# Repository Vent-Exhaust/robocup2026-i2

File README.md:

# robocup2026
# Vent Exhaust - RoboCup Singapore Soccer Infrared Junior 

<!--  -->

*Repository for the official electronic, mechanical, and software files of Vent Exhaust (VE) 1, formerly known as 2 Chairs.*

<p align="center">
  
</p>

## About

This repository is for **Vent Exhaust**, a Singapore RoboCup Infrared Soccer Junior team, and includes relevant design files and resources.

## Repository Structure

- **elec/** - PCB designs, schematics, and component footprints.
- **mech/** - 3D-printable files in **.3MF** and **.STL** formats; includes rendered images of the robot and its mirrored counterpart for reference and other files related to mechanical design.
- **code/** - PlatformIO firmware for the 3-layer robot architecture (Layer 1-3 Teensies / ESP32).
- **cam/** - MicroPython camera firmware (`cam.py`) running on an OpenMV H7 Plus, detecting goals and ball over serial.
- **branding/** - Official team branding and design assets.
- **media/** - Robot photos, gallery thumbnails, screenshots, and reference images used by the README and project documentation.

## Mechanical CAD

- [View the Fusion 360 model](https://a360.co/4tRNy74)

## Robot Gallery

<p align="center">

  <br>

</p>

## Robot Architecture

Three processors communicate over UART using a custom SerialComm packet protocol:

| Layer | Hardware | Role |
|-------|----------|------|
| Layer 1 | Teensy 4.0 | 32-LDR light ring - white line detection |
| Layer 2 | Teensy 4.0 | Main brain - strategy, X-drive motors, IMU heading hold, localisation, scoring |
| Layer 3 | Seeed XIAO ESP32-C3 | 28-IR sensor ring - ball detection + 4 DIP switches |
| Camera | OpenMV H7 Plus (MicroPython) | Dual-goal + ball vision -> serial CSV to Layer 2 |

## Branch Archive

`main` is the active branch. Previous development branches are preserved as
Git tags under `archive/`, such as `archive/i4-v3` and `archive/striker`.

## License & Copyright

Copyright 2026 Vent Exhaust. All rights reserved, except where otherwise stated.

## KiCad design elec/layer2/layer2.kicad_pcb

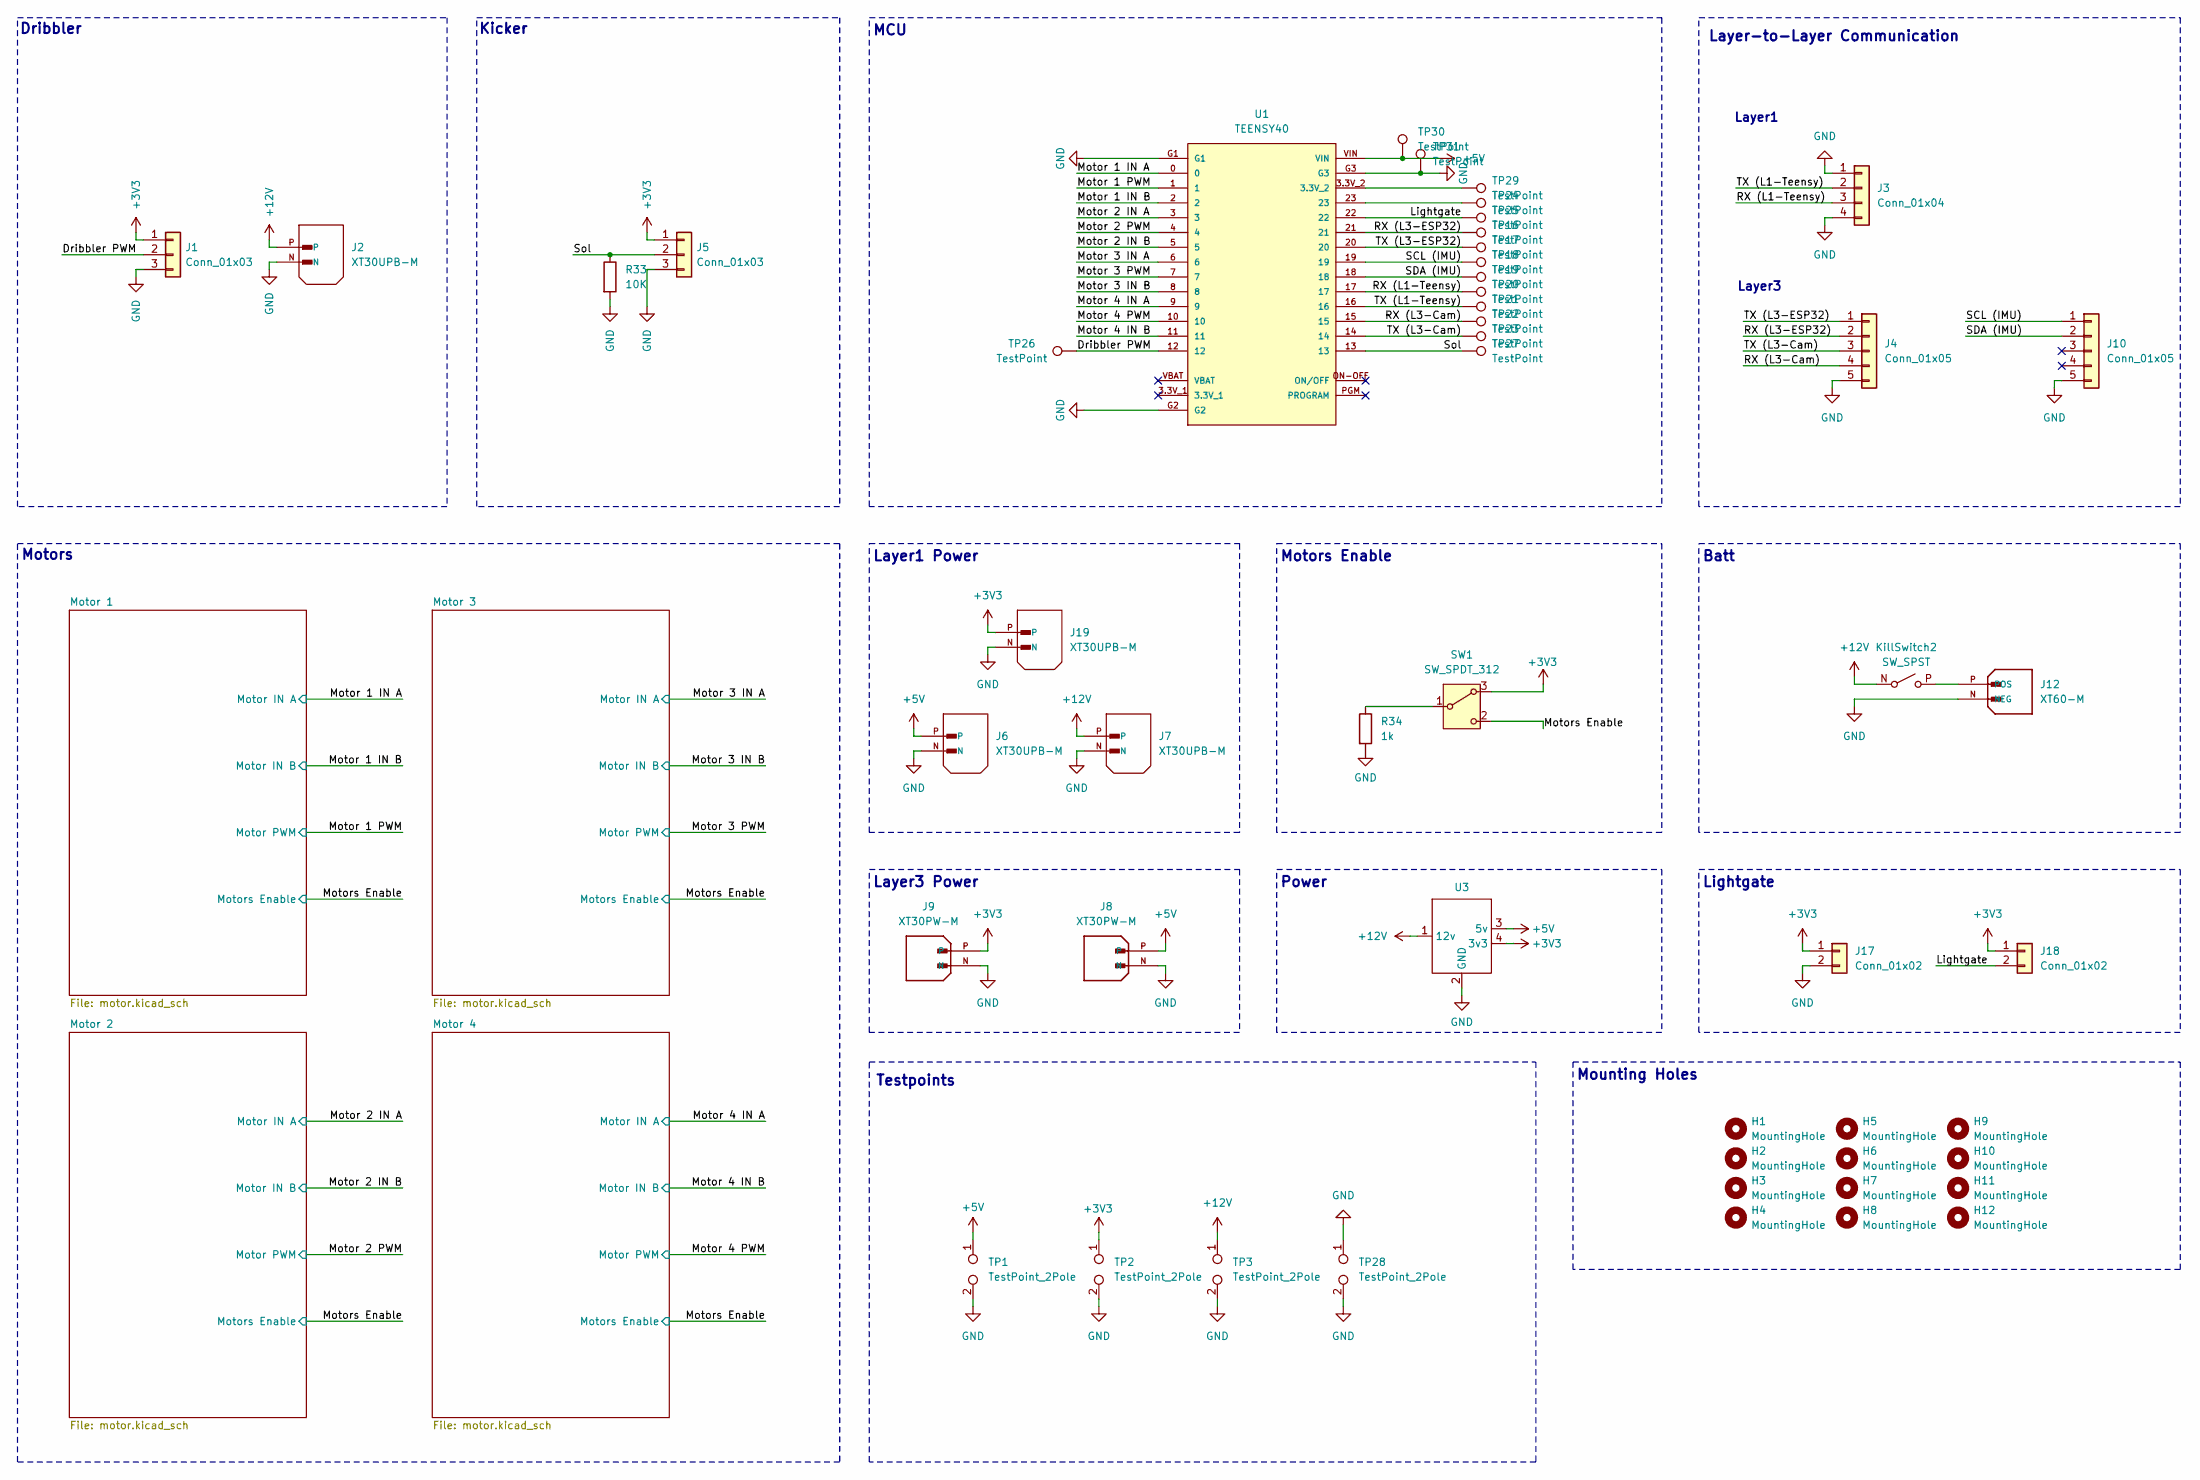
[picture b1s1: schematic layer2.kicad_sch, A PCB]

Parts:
H1, H2, H3, H4, H5, H6, H7, H8, H9, H10, H11, H12: MountingHole; MountingHole_3.2mm_M3_DIN965_Pad
J1, J5: Conn_01x03; JST_XH_B3B-XH-A_1x03_P2.50mm_Vertical
J2, J6, J7, J19: XT30UPB-M; AMASS_XT30UPB-M
J3: Conn_01x04; JST_XH_B4B-XH-A_1x04_P2.50mm_Vertical
J4, J10: Conn_01x05; JST_XH_B5B-XH-A_1x05_P2.50mm_Vertical
J8, J9: XT30PW-M; AMASS_XT30PW-M; PARTREV 1.2
J12: XT60-M; AMASS_XT60-M; PARTREV V1.2
J17, J18: Conn_01x02; JST_XH_B2B-XH-A_1x02_P2.50mm_Vertical
KillSwitch2: SW_SPST; AMASS_XT30UPB-M
R33: 10K; R_0603_1608Metric
R34: 1k; R_0603_1608Metric
SW1: SW_SPDT_312; SS12D00G3
TP1, TP2, TP3, TP28: TestPoint_2Pole; TestPoint_2Pads_Pitch2.54mm_Drill0.8mm
TP16, TP17, TP18, TP19, TP20, TP21, TP22, TP23, TP24, TP25, TP26, TP27, TP29, TP30, TP31: TestPoint; TestPoint_THTPad_D1.5mm_Drill0.7mm
U1: TEENSY40
U3: buck-module

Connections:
+3V3: J1.1, J5.1, J9.P, J17.1, J18.1, J19.P, SW1.3 (A), TP2.1, U3.4 (3v3); also elsewhere on the board
+5V: J6.P, J8.P, TP1.1, TP30.1, U1.VIN, U3.3 (5v)
+12V: J2.P, J7.P, KillSwitch2.N (A), TP3.1, U3.1 (12v); also elsewhere on the board
/Dribbler PWM: J1.2, TP26.1, U1.12
/Lightgate: J18.2, TP25.1, U1.22
/Motor 1 IN A: U1.0; also elsewhere on the board
/Motor 1 IN B: U1.2; also elsewhere on the board
/Motor 1 PWM: U1.1; also elsewhere on the board
/Motor 2 IN A: U1.3; also elsewhere on the board
/Motor 2 IN B: U1.5; also elsewhere on the board
/Motor 2 PWM: U1.4; also elsewhere on the board
/Motor 3 IN A: U1.6; also elsewhere on the board
/Motor 3 IN B: U1.8; also elsewhere on the board
/Motor 3 PWM: U1.7; also elsewhere on the board
/Motor 4 IN A: U1.9; also elsewhere on the board
/Motor 4 IN B: U1.11; also elsewhere on the board
/Motor 4 PWM: U1.10; also elsewhere on the board
/Motors Enable: R34.1, SW1.1 (B); also elsewhere on the board
/RX (L3-Cam: J4.3, TP23.1, U1.14
/RX (L3-ESP32): J4.1, TP17.1, U1.20
/SCL (IMU): J10.1, TP18.1, U1.19
/SDA (IMU): J10.2, TP19.1, U1.18
/Sol: J5.2, R33.1, TP27.1, U1.13
/TX (L3-Cam): J4.4, TP22.1, U1.15
/TX (L3-ESP32): J4.2, TP16.1, U1.21
GND: J1.3, J2.N, J3.1, J3.4, J4.5, J5.3, J6.N, J7.N, J8.N, J9.N, J10.5, J12.N (NEG), J17.2, J19.N, R33.2, R34.2, SW1.2 (C), TP1.2, TP2.2, TP3.2, TP28.1, TP28.2, TP31.1, U1.G1, U1.G2, U1.G3, U3.2 (GND); also elsewhere on the board
unnamed: J12.P (POS), KillSwitch2.P (B)
unnamed: TP24.1, U1.23
unnamed: TP29.1, U1.3.3V_2

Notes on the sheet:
Batt
Mounting Holes
Lightgate
Layer1
Power
Kicker
Dribbler
Motors
Testpoints
MCU
Layer3
Layer1 Power
Motors Enable
Layer-to-Layer Communication
Layer3 Power

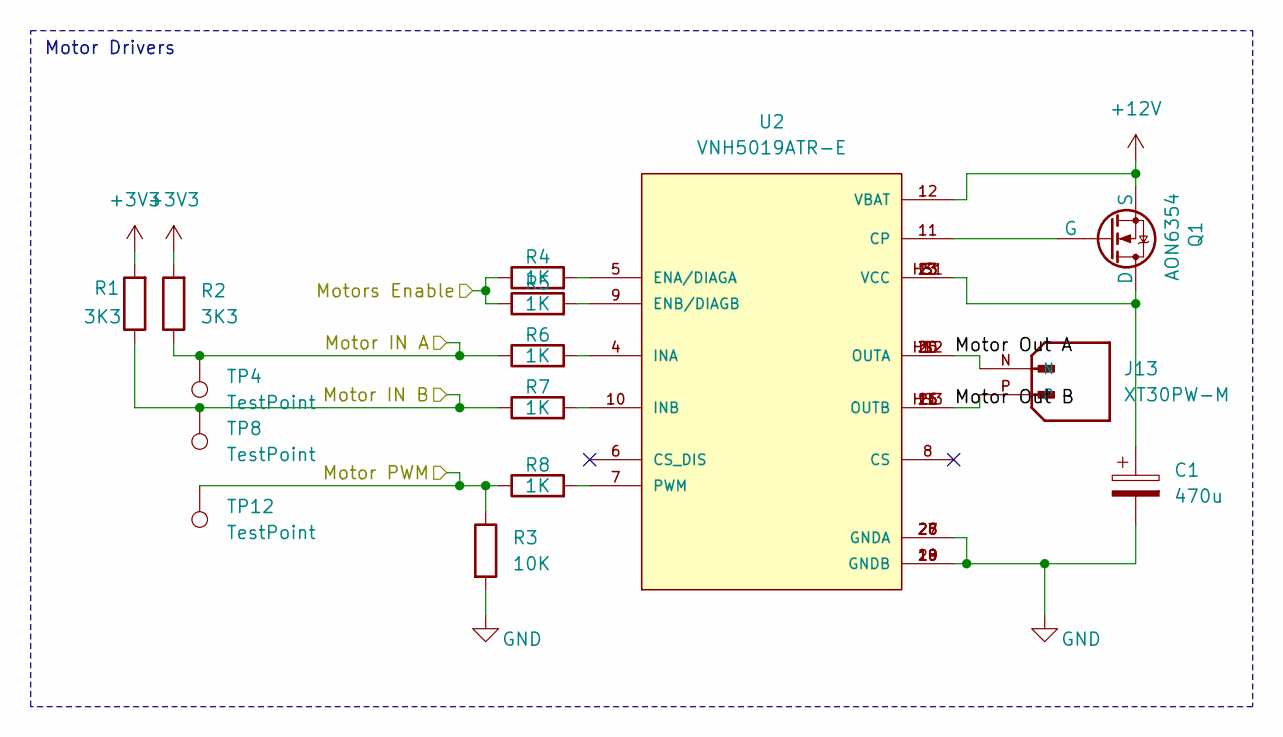
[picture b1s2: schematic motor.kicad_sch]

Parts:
C1: 470u; CP_Radial_D8.0mm_P3.50mm; LCSC C5162352
J13: XT30PW-M; AMASS_XT30PW-M; PARTREV 1.2
Q1: AON6354; 8-DFN (5x6)
R1, R2: 3K3; R_0603_1608Metric
R3: 10K; R_0603_1608Metric
R4, R5, R6, R7, R8: 1K; R_0603_1608Metric
TP4, TP8, TP12: TestPoint
U2: VNH5019ATR-E; PARTREV 11

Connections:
+3V3: R1.2, R2.2; also elsewhere on the board
+12V: Q1.1 (S), Q1.2 (S), Q1.3 (S), U2.12 (VBAT); also elsewhere on the board
/Motor 1 IN A: R2.1, R6.1, TP4.1; also elsewhere on the board
/Motor 1 IN B: R1.1, R7.1, TP8.1; also elsewhere on the board
/Motor 1 PWM: R3.1, R8.1, TP12.1; also elsewhere on the board
/Motor 1/Motor Out A: J13.N, U2.1 (OUTA), U2.25 (OUTA), U2.30 (OUTA), U2.HS2 (OUTA)
/Motor 1/Motor Out B: J13.P, U2.15 (OUTB), U2.16 (OUTB), U2.21 (OUTB), U2.HS3 (OUTB)
/Motors Enable: R4.1, R5.1; also elsewhere on the board
GND: C1.2, R3.2, U2.18 (GNDB), U2.19 (GNDB), U2.20 (GNDB), U2.26 (GNDA), U2.27 (GNDA), U2.28 (GNDA); also elsewhere on the board
unnamed: C1.1, Q1.5 (D), Q1.6 (D), Q1.7 (D), Q1.8 (D), Q1.9 (D), U2.3 (VCC), U2.13 (VCC), U2.23 (VCC), U2.HS1 (VCC)
unnamed: Q1.4 (G), U2.11 (CP)
unnamed: R4.2, U2.5 (ENA/DIAGA)
unnamed: R5.2, U2.9 (ENB/DIAGB)
unnamed: R6.2, U2.4 (INA)
unnamed: R7.2, U2.10 (INB)
unnamed: R8.2, U2.7 (PWM)

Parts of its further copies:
C2, C3, C4: 470u; CP_Radial_D8.0mm_P3.50mm; LCSC C5162352
J14, J15, J16: XT30PW-M; AMASS_XT30PW-M; PARTREV 1.2
Q2, Q3, Q4: AON6354; 8-DFN (5x6)
R9, R10, R17, R18, R25, R26: 3K3; R_0603_1608Metric
R11, R19, R27: 10K; R_0603_1608Metric
R12, R13, R14, R15, R16, R20, R21, R22, R23, R24, R28, R29, R30, R31, R32: 1K; R_0603_1608Metric
TP5, TP6, TP7, TP9, TP10, TP11, TP13, TP14, TP15: TestPoint
U4, U6, U8: VNH5019ATR-E; PARTREV 11

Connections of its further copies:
+3V3: R9.2, R10.2, R17.2, R18.2, R25.2, R26.2; also elsewhere on the board
+12V: Q2.1 (S), Q2.2 (S), Q2.3 (S), Q3.1 (S), Q3.2 (S), Q3.3 (S), Q4.1 (S), Q4.2 (S), Q4.3 (S), U4.12 (VBAT), U6.12 (VBAT), U8.12 (VBAT); also elsewhere on the board
/Motor 2 IN A: R10.1, R14.1, TP5.1; also elsewhere on the board
/Motor 2 IN B: R9.1, R15.1, TP9.1; also elsewhere on the board
/Motor 2 PWM: R11.1, R16.1, TP13.1; also elsewhere on the board
/Motor 2/Motor Out A: J14.N, U4.1 (OUTA), U4.25 (OUTA), U4.30 (OUTA), U4.HS2 (OUTA)
/Motor 2/Motor Out B: J14.P, U4.15 (OUTB), U4.16 (OUTB), U4.21 (OUTB), U4.HS3 (OUTB)
/Motor 3 IN A: R18.1, R22.1, TP6.1; also elsewhere on the board
/Motor 3 IN B: R17.1, R23.1, TP10.1; also elsewhere on the board
/Motor 3 PWM: R19.1, R24.1, TP14.1; also elsewhere on the board
/Motor 3/Motor Out A: J15.N, U6.1 (OUTA), U6.25 (OUTA), U6.30 (OUTA), U6.HS2 (OUTA)
/Motor 3/Motor Out B: J15.P, U6.15 (OUTB), U6.16 (OUTB), U6.21 (OUTB), U6.HS3 (OUTB)
/Motor 4 IN A: R26.1, R30.1, TP7.1; also elsewhere on the board
/Motor 4 IN B: R25.1, R31.1, TP11.1; also elsewhere on the board
/Motor 4 PWM: R27.1, R32.1, TP15.1; also elsewhere on the board
/Motor 4/Motor Out A: J16.N, U8.1 (OUTA), U8.25 (OUTA), U8.30 (OUTA), U8.HS2 (OUTA)
/Motor 4/Motor Out B: J16.P, U8.15 (OUTB), U8.16 (OUTB), U8.21 (OUTB), U8.HS3 (OUTB)
/Motors Enable: R12.1, R13.1, R20.1, R21.1, R28.1, R29.1; also elsewhere on the board
GND: C2.2, C3.2, C4.2, R11.2, R19.2, R27.2, U4.18 (GNDB), U4.19 (GNDB), U4.20 (GNDB), U4.26 (GNDA), U4.27 (GNDA), U4.28 (GNDA), U6.18 (GNDB), U6.19 (GNDB), U6.20 (GNDB), U6.26 (GNDA), U6.27 (GNDA), U6.28 (GNDA), U8.18 (GNDB), U8.19 (GNDB), U8.20 (GNDB), U8.26 (GNDA), U8.27 (GNDA), U8.28 (GNDA); also elsewhere on the board
unnamed: C2.1, Q2.5 (D), Q2.6 (D), Q2.7 (D), Q2.8 (D), Q2.9 (D), U4.3 (VCC), U4.13 (VCC), U4.23 (VCC), U4.HS1 (VCC)
unnamed: C3.1, Q3.5 (D), Q3.6 (D), Q3.7 (D), Q3.8 (D), Q3.9 (D), U6.3 (VCC), U6.13 (VCC), U6.23 (VCC), U6.HS1 (VCC)
unnamed: C4.1, Q4.5 (D), Q4.6 (D), Q4.7 (D), Q4.8 (D), Q4.9 (D), U8.3 (VCC), U8.13 (VCC), U8.23 (VCC), U8.HS1 (VCC)
unnamed: Q2.4 (G), U4.11 (CP)
unnamed: Q3.4 (G), U6.11 (CP)
unnamed: Q4.4 (G), U8.11 (CP)
unnamed: R12.2, U4.5 (ENA/DIAGA)
unnamed: R13.2, U4.9 (ENB/DIAGB)
unnamed: R14.2, U4.4 (INA)
unnamed: R15.2, U4.10 (INB)
unnamed: R16.2, U4.7 (PWM)
unnamed: R20.2, U6.5 (ENA/DIAGA)
unnamed: R21.2, U6.9 (ENB/DIAGB)
unnamed: R22.2, U6.4 (INA)
unnamed: R23.2, U6.10 (INB)
unnamed: R24.2, U6.7 (PWM)
unnamed: R28.2, U8.5 (ENA/DIAGA)
unnamed: R29.2, U8.9 (ENB/DIAGB)
unnamed: R30.2, U8.4 (INA)
unnamed: R31.2, U8.10 (INB)
unnamed: R32.2, U8.7 (PWM)

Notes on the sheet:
Motor Drivers

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
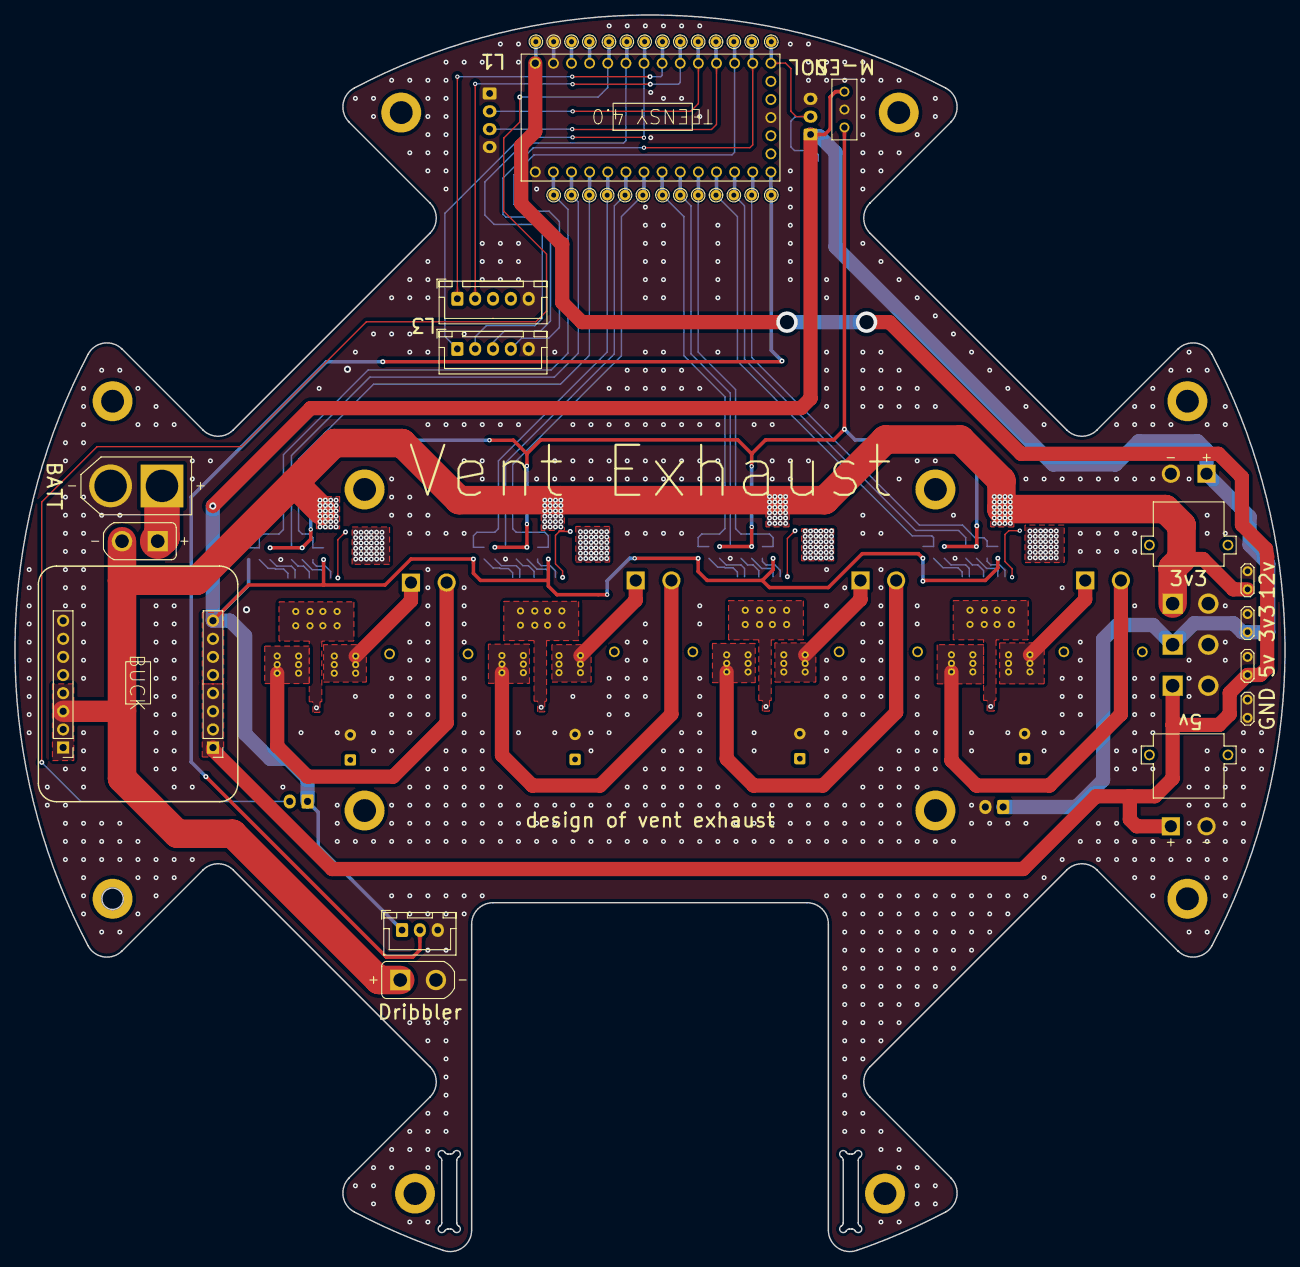
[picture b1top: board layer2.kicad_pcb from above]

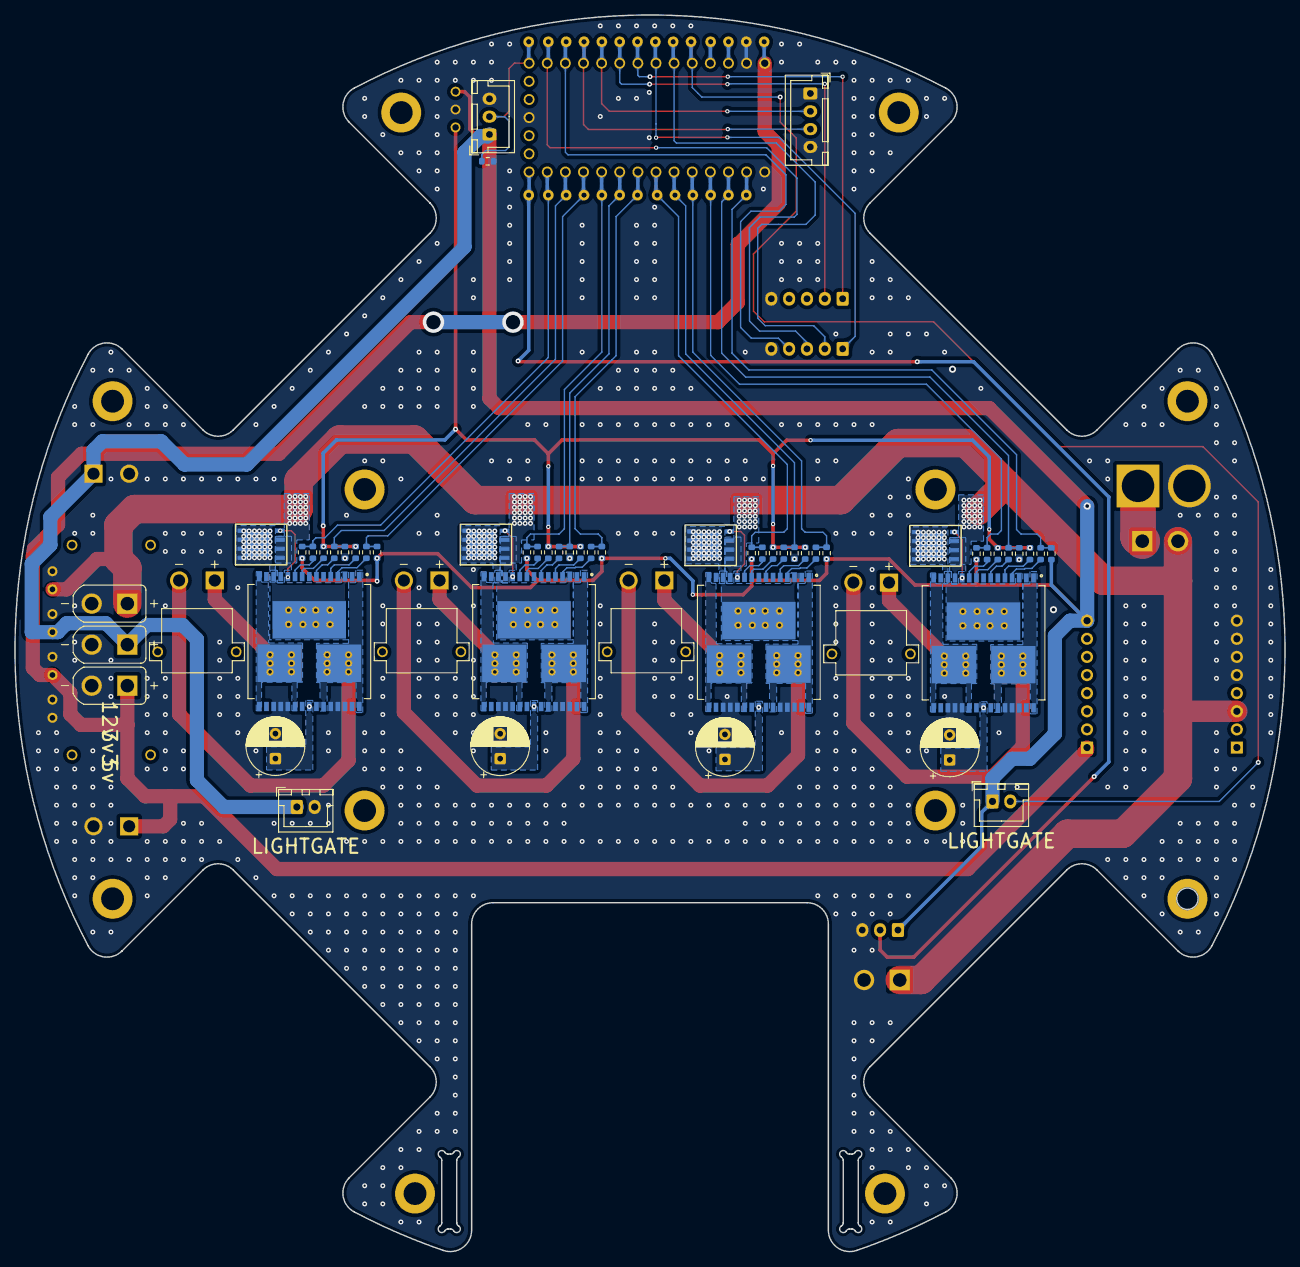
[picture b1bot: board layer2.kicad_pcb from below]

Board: 2 copper layers, 178.0 x 173.3 mm, 110 parts (56 on the bottom side), 67 nets.

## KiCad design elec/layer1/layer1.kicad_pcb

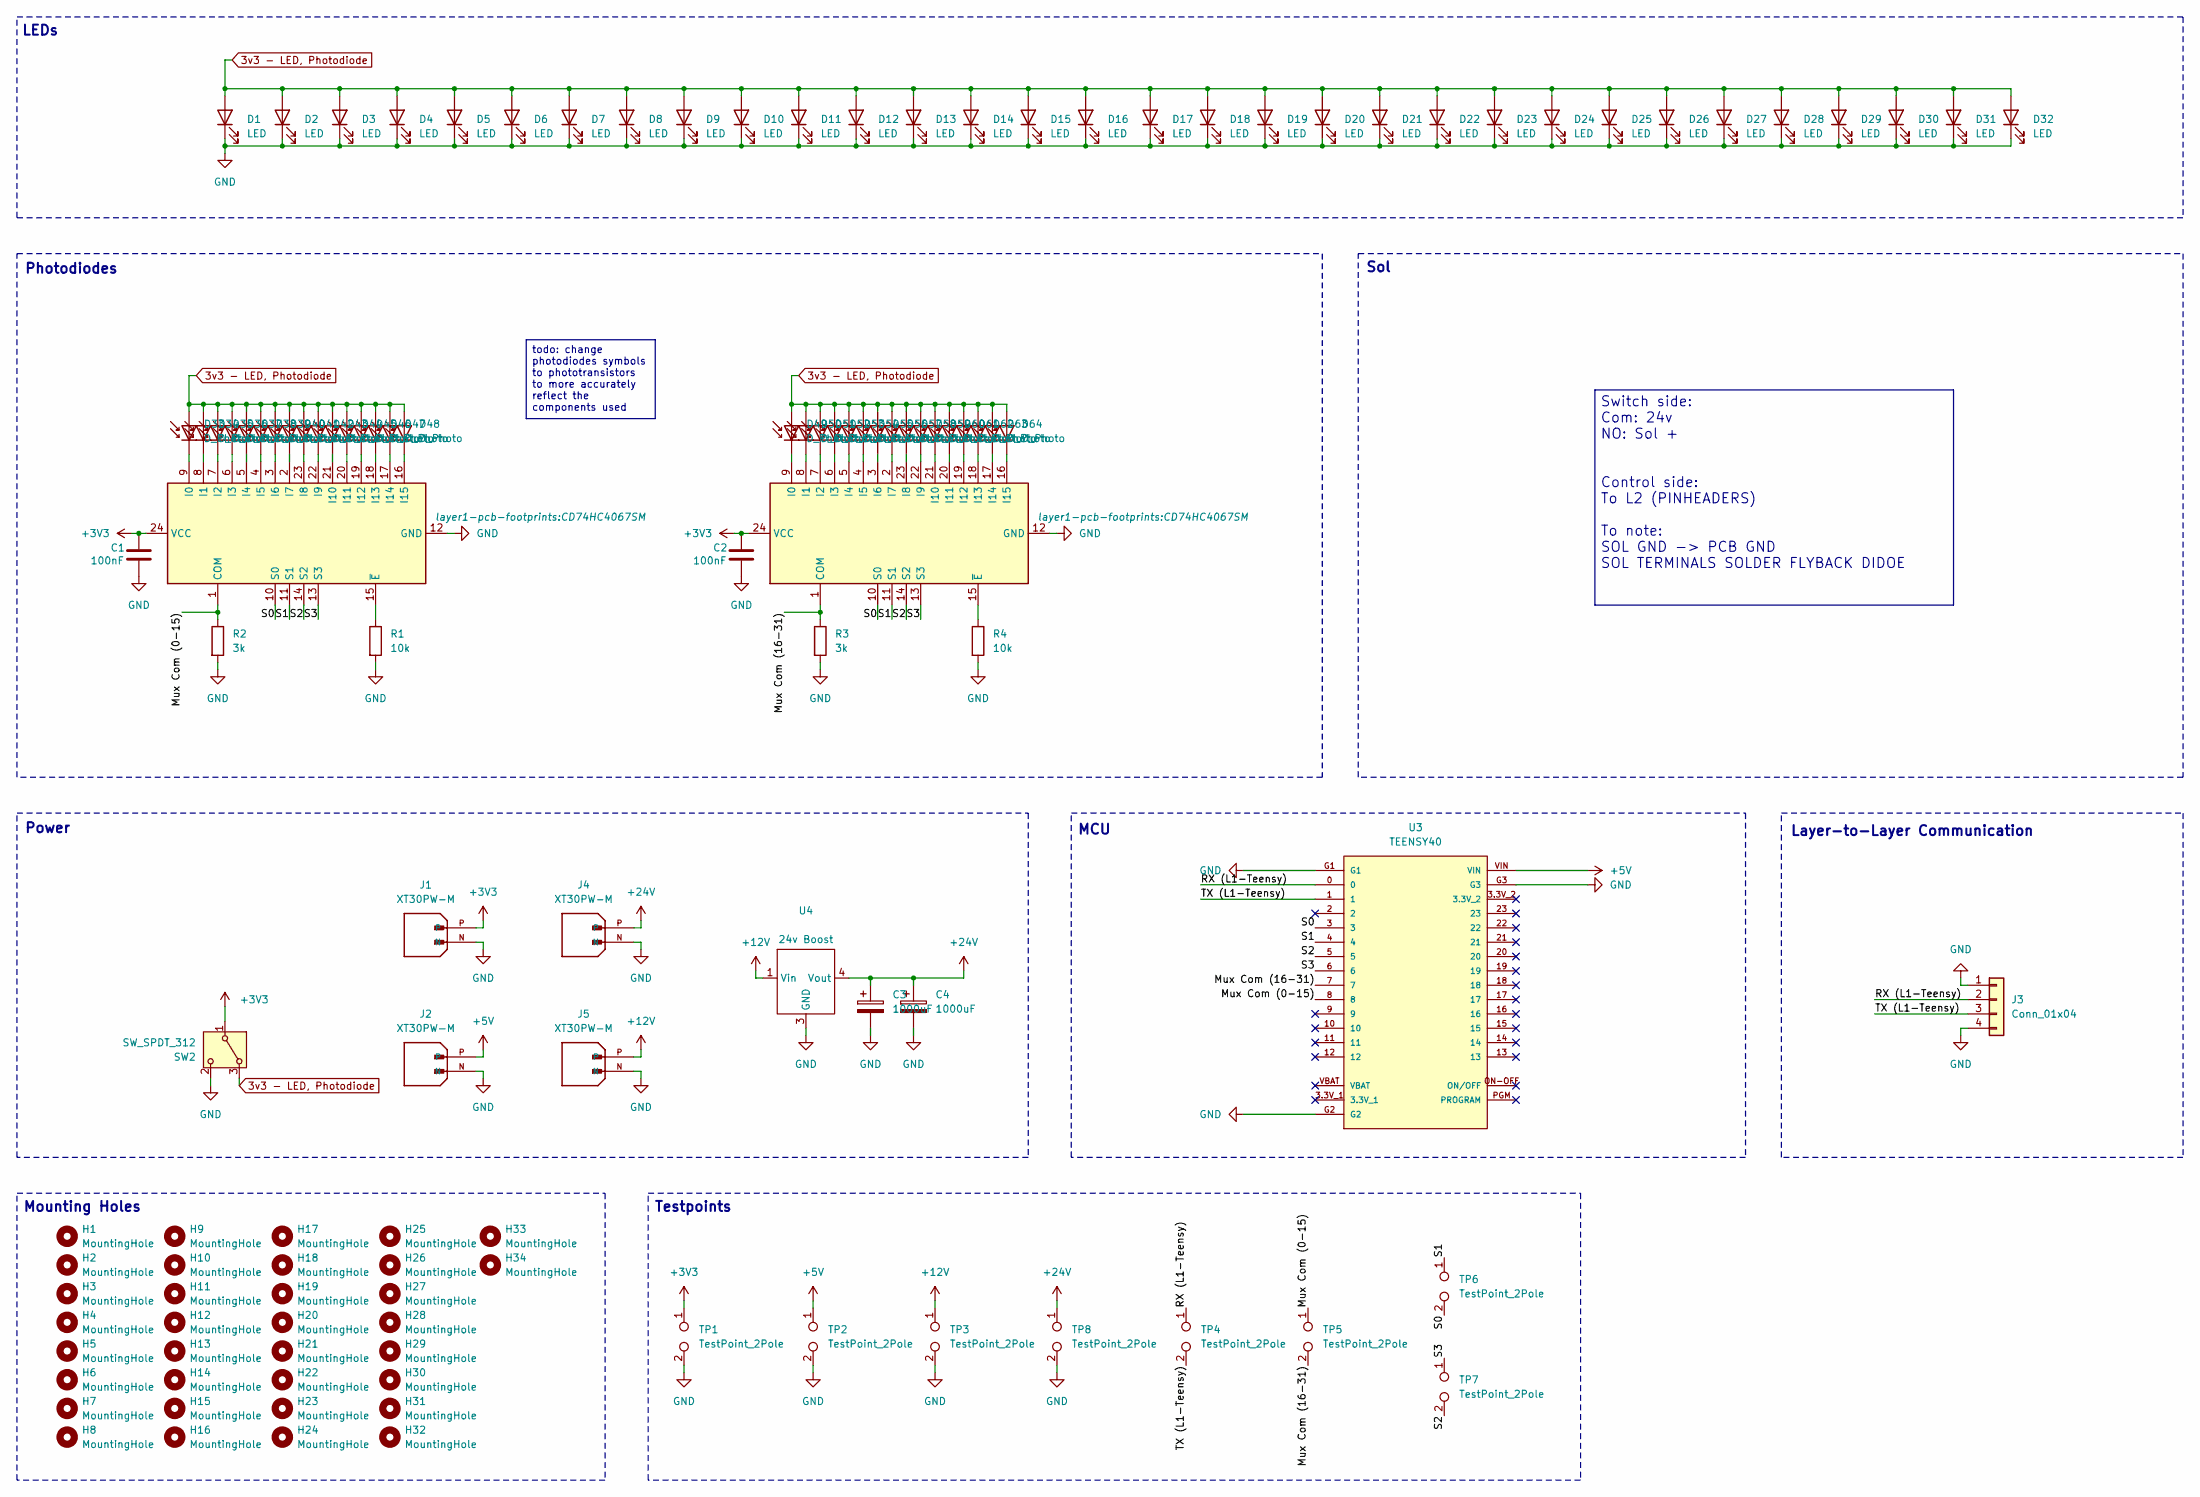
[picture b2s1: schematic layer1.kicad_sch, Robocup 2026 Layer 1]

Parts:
C1, C2: 100nF; C_0603_1608Metric
C3, C4: 1000uF; CP_Radial_D16.0mm_P7.50mm
D1, D2, D3, D4, D5, D6, D7, D8, D9, D10, D11, D12, D13, D14, D15, D16, D17, D18, D19, D20, D21, D22, D23, D24, D25, D26, D27, D28, D29, D30, D31, D32: LED; LED_PLCC_2835
D33, D34, D35, D36, D37, D38, D39, D40, D41, D42, D43, D44, D45, D46, D47, D48, D49, D50, D51, D52, D53, D54, D55, D56, D57, D58, D59, D60, D61, D62, D63, D64: D_Photo; D_0603_1608Metric
H1, H2, H33, H34: MountingHole; MountingHole_2.2mm_M2_DIN965_Pad_TopBottom
H3, H4, H5, H6, H7, H8, H9, H10, H11, H12, H13, H14, H15, H16, H17, H18, H19, H20, H21, H22, H23, H24, H25, H26, H27, H28, H29, H30, H31, H32: MountingHole; MountingHole_3.2mm_M3_DIN965_Pad_TopBottom
J1, J2, J4, J5: XT30PW-M; AMASS_XT30PW-M; PARTREV 1.2
J3: Conn_01x04; JST_XH_B4B-XH-AM_1x04_P2.50mm_Vertical
R1, R4: 10k; C_0603_1608Metric
R2, R3: 3k; C_0603_1608Metric
SW2: SW_SPDT_312; JST_XH_B3B-XH-A_1x03_P2.50mm_Vertical
TP1, TP2, TP3, TP4, TP5, TP6, TP7, TP8: TestPoint_2Pole; TestPoint_2Pads_Pitch2.54mm_Drill0.8mm
U1, U2: CD74HC4067SM
U3: TEENSY40
U4: boost-module

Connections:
3v3 - LED, Photodiode: D1.2 (A), D2.2 (A), D3.2 (A), D4.2 (A), D5.2 (A), D6.2 (A), D7.2 (A), D8.2 (A), D9.2 (A), D10.2 (A), D11.2 (A), D12.2 (A), D13.2 (A), D14.2 (A), D15.2 (A), D16.2 (A), D17.2 (A), D18.2 (A), D19.2 (A), D20.2 (A), D21.2 (A), D22.2 (A), D23.2 (A), D24.2 (A), D25.2 (A), D26.2 (A), D27.2 (A), D28.2 (A), D29.2 (A), D30.2 (A), D31.2 (A), D32.2 (A), D33.2 (A), D34.2 (A), D35.2 (A), D36.2 (A), D37.2 (A), D38.2 (A), D39.2 (A), D40.2 (A), D41.2 (A), D42.2 (A), D43.2 (A), D44.2 (A), D45.2 (A), D46.2 (A), D47.2 (A), D48.2 (A), D49.2 (A), D50.2 (A), D51.2 (A), D52.2 (A), D53.2 (A), D54.2 (A), D55.2 (A), D56.2 (A), D57.2 (A), D58.2 (A), D59.2 (A), D60.2 (A), D61.2 (A), D62.2 (A), D63.2 (A), D64.2 (A), SW2.3 (A)
+3V3: C1.1, C2.1, J1.P, SW2.1 (B), TP1.1, U1.24 (VCC), U2.24 (VCC)
+5V: J2.P, TP2.1, U3.VIN
+12V: J5.P, TP3.1, U4.1 (Vin)
+24V: C3.1, C4.1, J4.P, TP8.1, U4.4 (Vout)
/Mux Com (0-15): R2.1, TP5.1, U1.1 (COM), U3.8
/Mux Com (16-31): R3.1, TP5.2, U2.1 (COM), U3.7
/RX (L1-Teensy): J3.2, TP4.1, U3.0
/S0: TP6.2, U1.10 (S0), U2.10 (S0), U3.3
/S1: TP6.1, U1.11 (S1), U2.11 (S1), U3.4
/S2: TP7.2, U1.14 (S2), U2.14 (S2), U3.5
/S3: TP7.1, U1.13 (S3), U2.13 (S3), U3.6
/TX (L1-Teensy): J3.3, TP4.2, U3.1
GND: C1.2, C2.2, C3.2, C4.2, D1.1 (K), D2.1 (K), D3.1 (K), D4.1 (K), D5.1 (K), D6.1 (K), D7.1 (K), D8.1 (K), D9.1 (K), D10.1 (K), D11.1 (K), D12.1 (K), D13.1 (K), D14.1 (K), D15.1 (K), D16.1 (K), D17.1 (K), D18.1 (K), D19.1 (K), D20.1 (K), D21.1 (K), D22.1 (K), D23.1 (K), D24.1 (K), D25.1 (K), D26.1 (K), D27.1 (K), D28.1 (K), D29.1 (K), D30.1 (K), D31.1 (K), D32.1 (K), J1.N, J2.N, J3.1, J3.4, J4.N, J5.N, R1.2, R2.2, R3.2, R4.2, SW2.2 (C), TP1.2, TP2.2, TP3.2, TP8.2, U1.12 (GND), U2.12 (GND), U3.G1, U3.G2, U3.G3, U4.3 (GND)
unnamed: D33.1 (K), U1.9 (I0)
unnamed: D34.1 (K), U1.8 (I1)
unnamed: D35.1 (K), U1.7 (I2)
unnamed: D36.1 (K), U1.6 (I3)
unnamed: D37.1 (K), U1.5 (I4)
unnamed: D38.1 (K), U1.4 (I5)
unnamed: D39.1 (K), U1.3 (I6)
unnamed: D40.1 (K), U1.2 (I7)
unnamed: D41.1 (K), U1.23 (I8)
unnamed: D42.1 (K), U1.22 (I9)
unnamed: D43.1 (K), U1.21 (I10)
unnamed: D44.1 (K), U1.20 (I11)
unnamed: D45.1 (K), U1.19 (I12)
unnamed: D46.1 (K), U1.18 (I13)
unnamed: D47.1 (K), U1.17 (I14)
unnamed: D48.1 (K), U1.16 (I15)
unnamed: D49.1 (K), U2.9 (I0)
unnamed: D50.1 (K), U2.8 (I1)
unnamed: D51.1 (K), U2.7 (I2)
unnamed: D52.1 (K), U2.6 (I3)
unnamed: D53.1 (K), U2.5 (I4)
unnamed: D54.1 (K), U2.4 (I5)
unnamed: D55.1 (K), U2.3 (I6)
unnamed: D56.1 (K), U2.2 (I7)
unnamed: D57.1 (K), U2.23 (I8)
unnamed: D58.1 (K), U2.22 (I9)
unnamed: D59.1 (K), U2.21 (I10)
unnamed: D60.1 (K), U2.20 (I11)
unnamed: D61.1 (K), U2.19 (I12)
unnamed: D62.1 (K), U2.18 (I13)
unnamed: D63.1 (K), U2.17 (I14)
unnamed: D64.1 (K), U2.16 (I15)
unnamed: R1.1, U1.15 (~E)
unnamed: R4.1, U2.15 (~E)

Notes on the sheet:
Layer-to-Layer Communication
Testpoints
MCU
Power
Mounting Holes
LEDs
Photodiodes
Sol
todo: change photodiodes symbols to phototransistors to more accurately reflect the components used
Switch side: Com: 24v NO: Sol + Control side: To L2 (PINHEADERS) To note: SOL GND -> PCB GND SOL TERMINALS SOLDER FLYBACK DIDOE

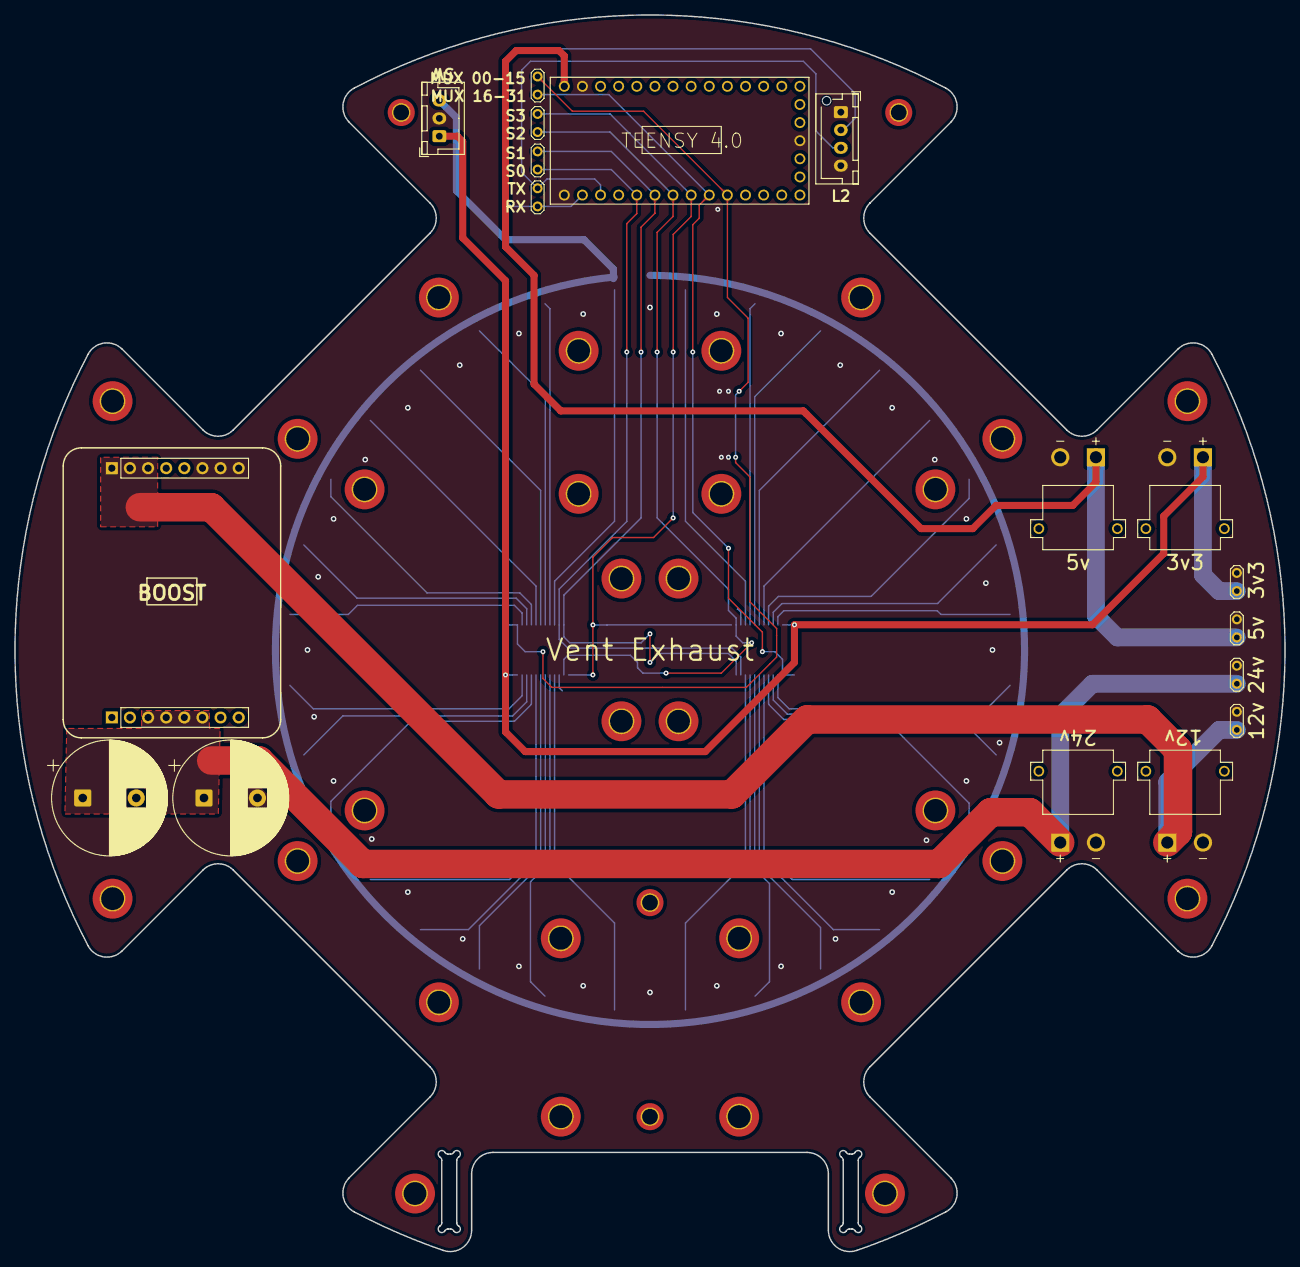
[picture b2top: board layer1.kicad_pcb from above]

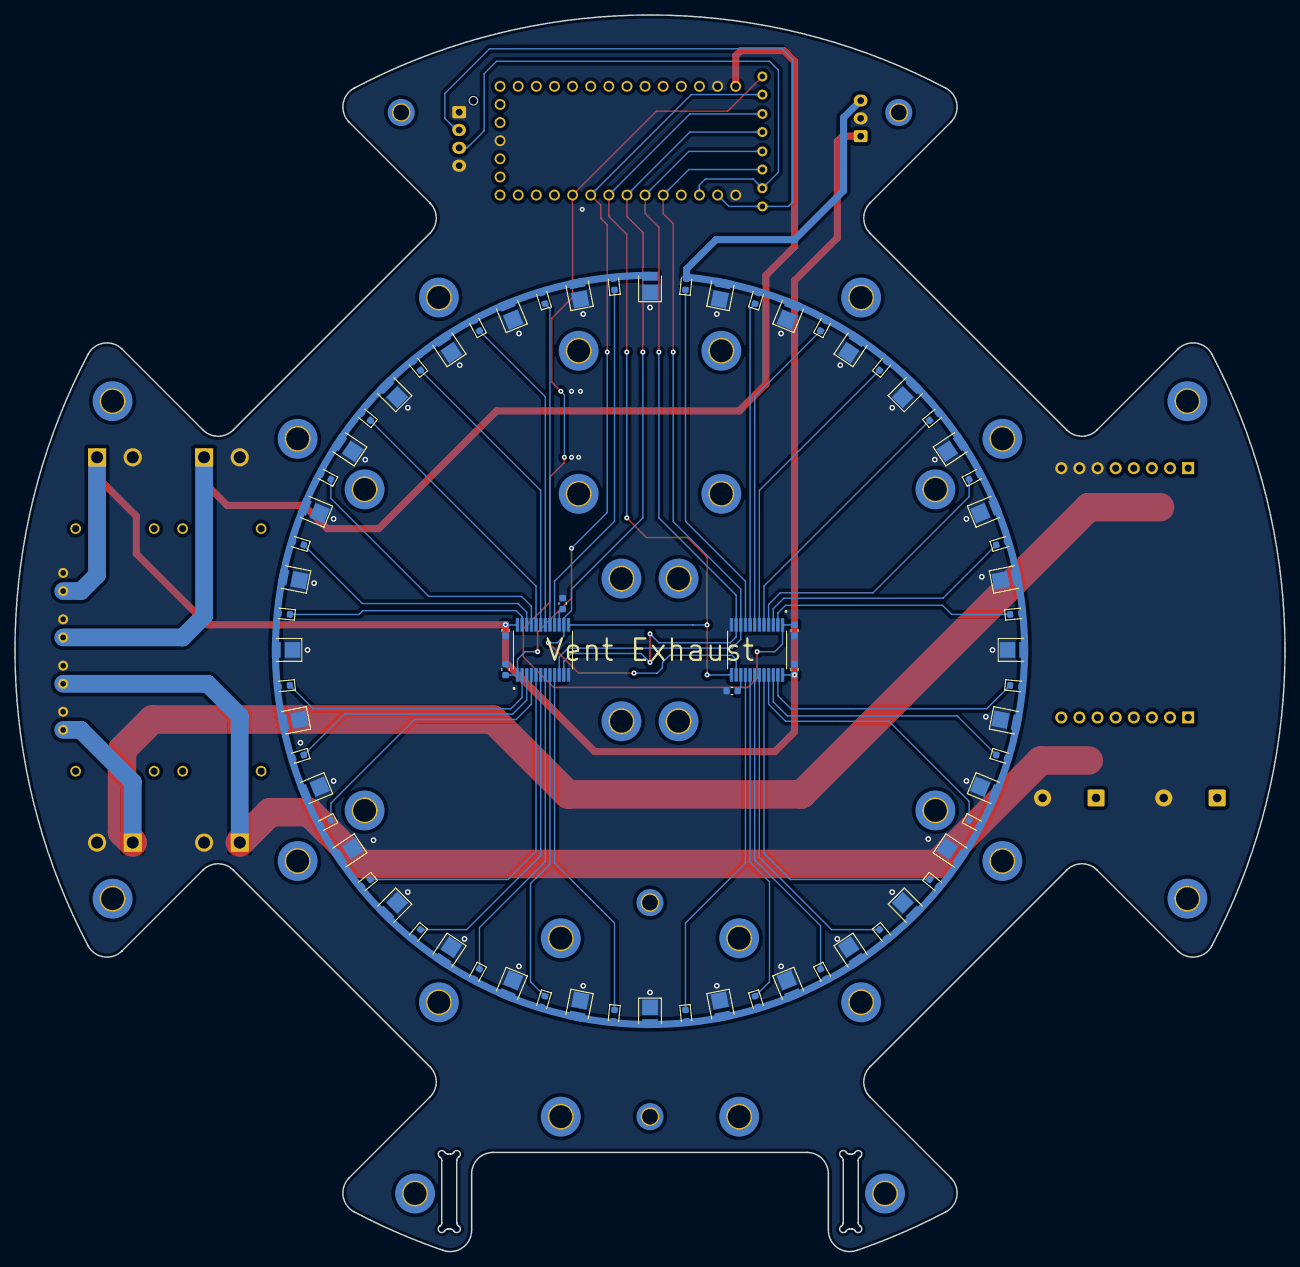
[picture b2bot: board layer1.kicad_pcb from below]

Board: 2 copper layers, 178.0 x 173.3 mm, 124 parts (72 on the bottom side), 48 nets.

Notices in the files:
elec/modules/Tofs/SparkFun_Qwiic_Pulsed_Coherent_Radar_Sensor_Breakout-XM125_v10/XM125_Breakout.kicad_sch:
Released under the Creative Commons
https://creativecommons.org/licenses/by-sa/4.0
